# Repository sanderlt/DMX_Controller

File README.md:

# DMX512 LED Controller
Arduino DMX Controller. 48(16RGB) outputs. Based on 74HC595 Shift Registers.
Working voltage from 5 to 24v.

Files created in KiCad 7.0.1 and Arduino IDE 2.2.1

Firmware contain 20 programs. To switch betwin program please choose DMX address and fader to use specific program(see dmx_ctrl_nano_v.1.ino line 124 for options).

Planning to add smd AVR(or ARM) version

Demo video:

KiCad 3d wiew:

KiCad PCB editor view:

Assembly Process(you can see earliest pcb version):

Final View:

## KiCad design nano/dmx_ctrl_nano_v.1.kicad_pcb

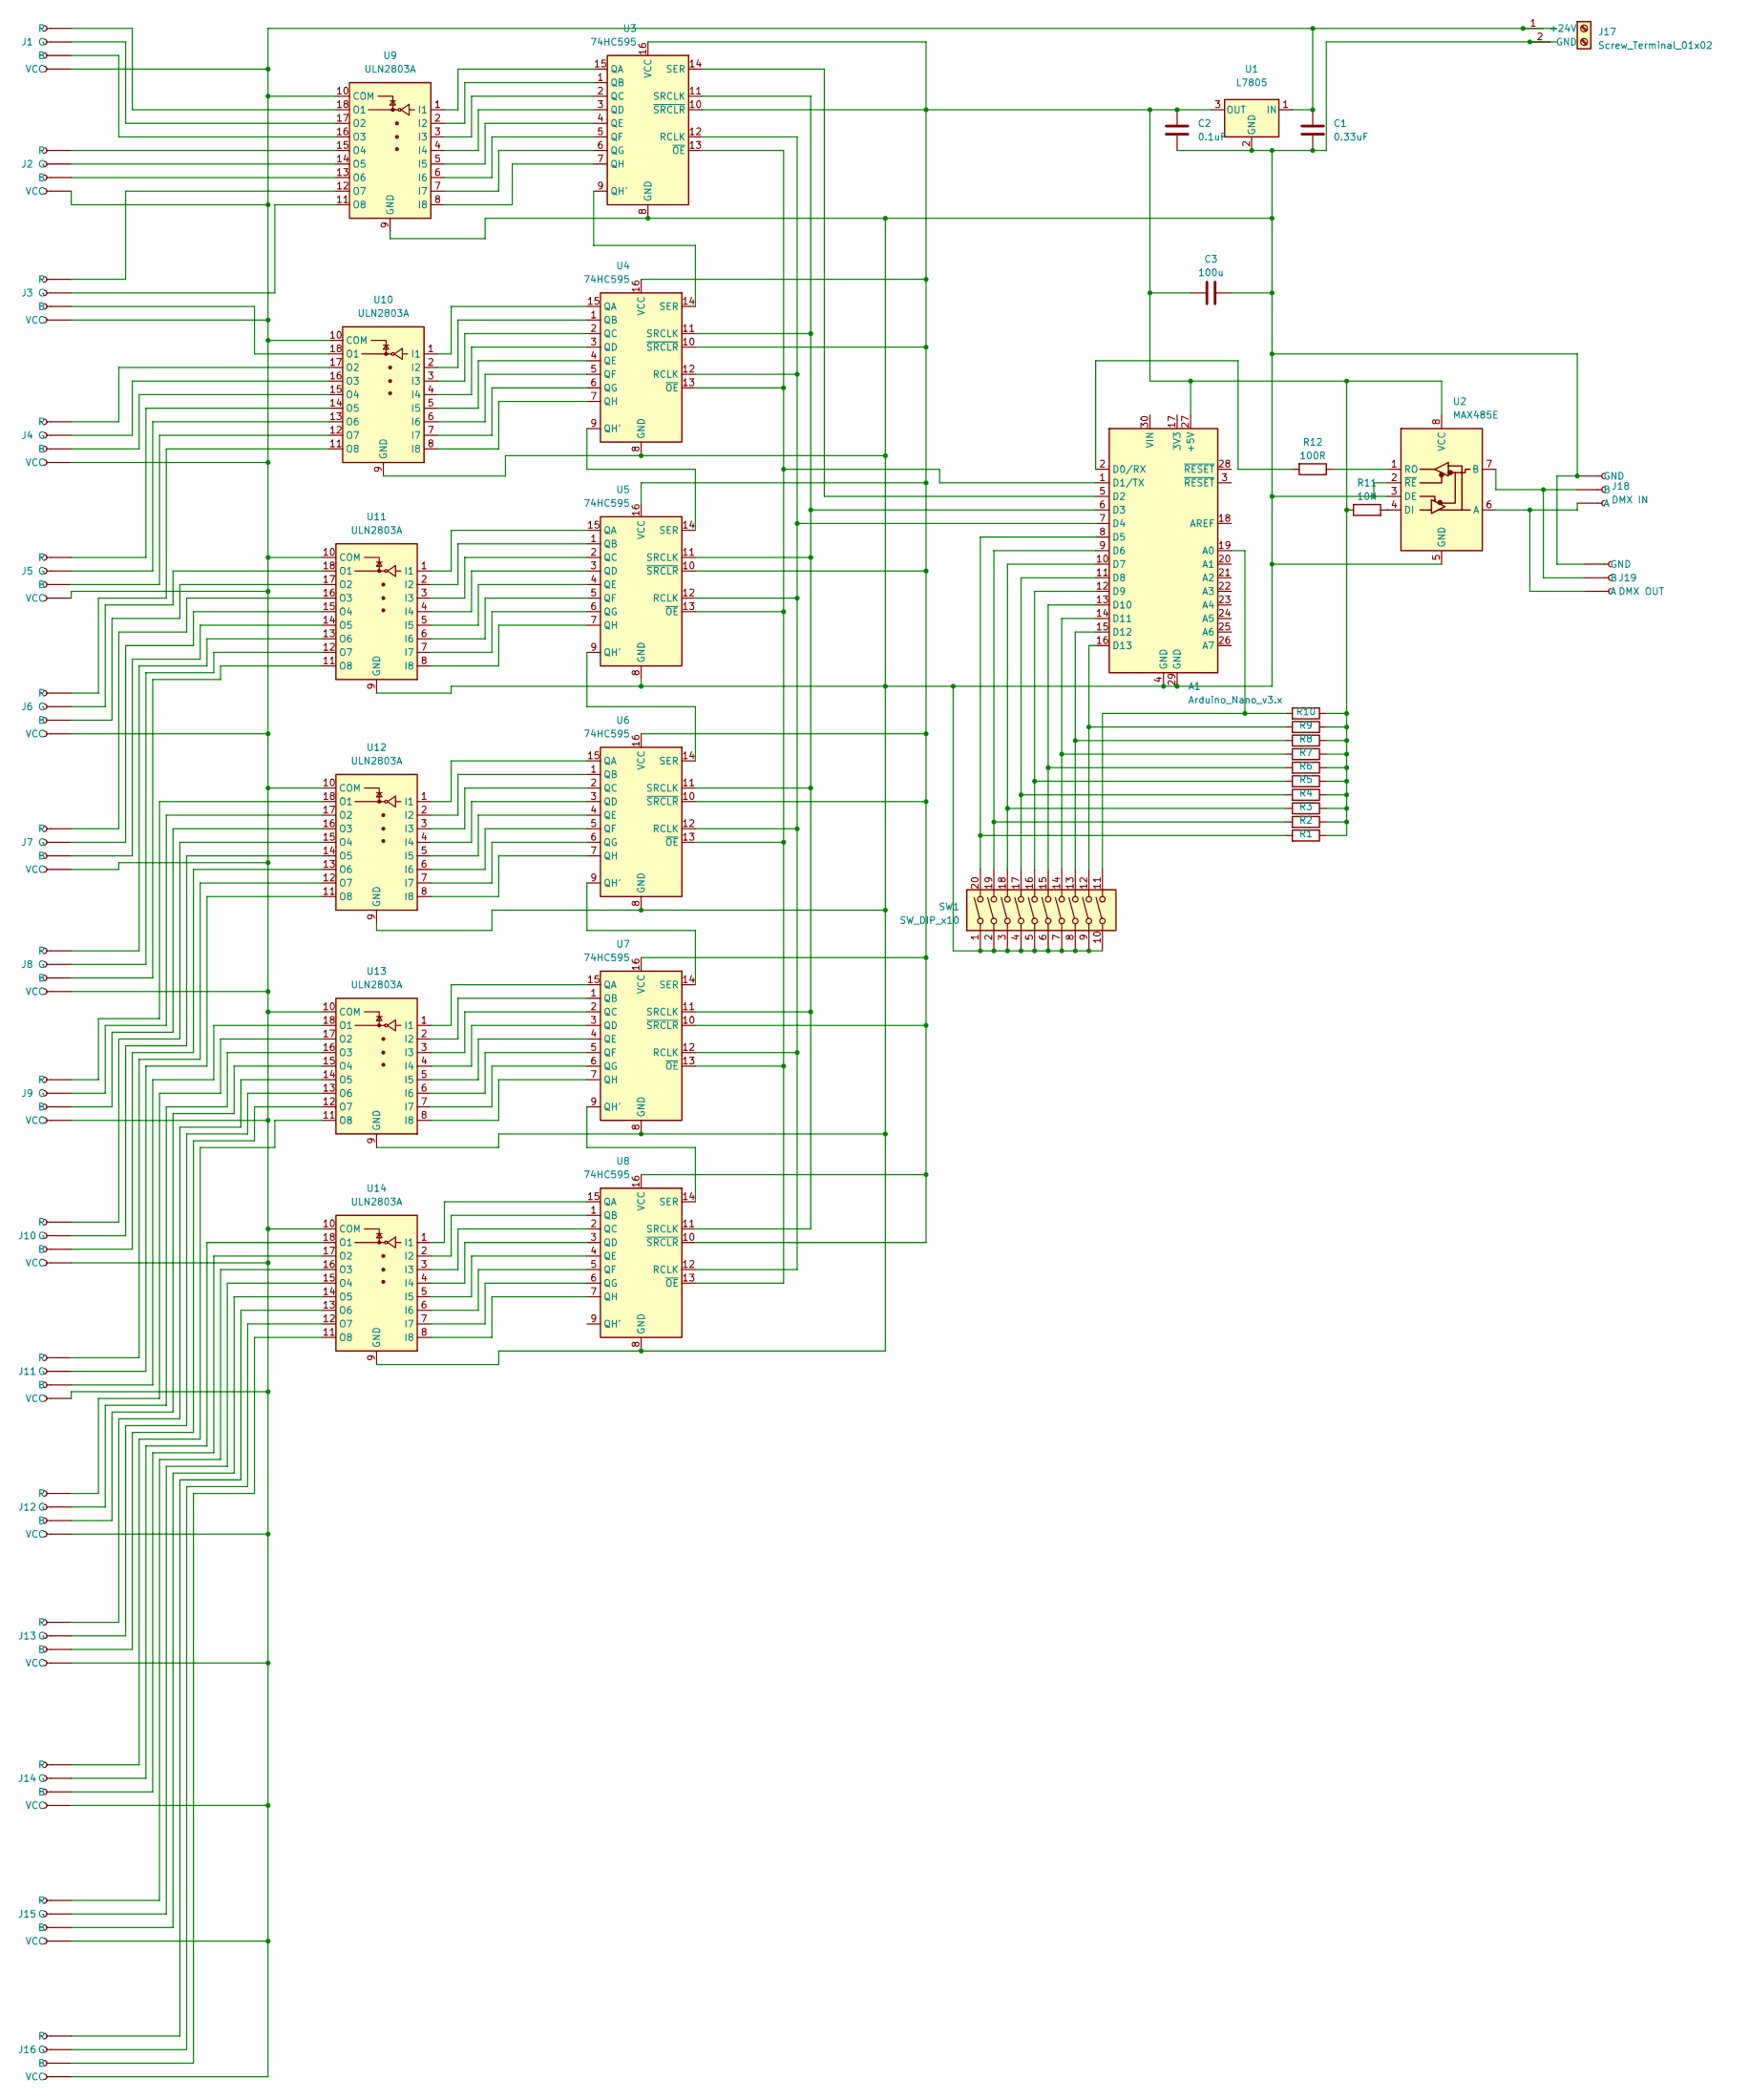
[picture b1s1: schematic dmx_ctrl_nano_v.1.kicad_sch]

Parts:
A1: Arduino_Nano_v3.x; Arduino_Nano
C1: 0.33uF; C_Axial_L3.8mm_D2.6mm_P7.50mm_Horizontal
C2: 0.1uF; C_Axial_L3.8mm_D2.6mm_P7.50mm_Horizontal
C3: 100u; C_Axial_L3.8mm_D2.6mm_P7.50mm_Horizontal
J1, J2, J3, J4, J5, J6, J7, J8, J9, J10, J11, J12, J13, J14, J15, J16: Conn_01x04_Female; TerminalBlock_4Ucon_1x04_P3.50mm_Vertical
J17: Screw_Terminal_01x02; TerminalBlock_bornier-2_P5.08mm
J18: DMX IN; TerminalBlock_4Ucon_1x03_P3.50mm_Vertical
J19: DMX OUT; TerminalBlock_4Ucon_1x03_P3.50mm_Vertical
R1, R2, R3, R4, R5, R6, R7, R8, R9, R10, R11: 10K; R_Axial_DIN0207_L6.3mm_D2.5mm_P2.54mm_Vertical
R12: 100R; R_Axial_DIN0207_L6.3mm_D2.5mm_P2.54mm_Vertical
SW1: SW_DIP_x10; DIP-20_W7.62mm
U1: L7805; TO-220F-3_Horizontal_TabDown
U2: MAX485E; DIP-8_W7.62mm
U3, U4, U5, U6, U7, U8: 74HC595; DIP-16_W7.62mm
U9, U10, U11, U12, U13, U14: ULN2803A; DIP-18_W7.62mm_LongPads

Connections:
unnamed: A1.27 (+5V), C2.1, C3.1, R1.1, R2.1, R3.1, R4.1, R5.1, R6.1, R7.1, R8.1, R9.1, R10.1, R11.1, U1.3 (OUT), U2.8 (VCC), U3.10 (~SRCLR), U3.16 (VCC), U4.10 (~SRCLR), U4.16 (VCC), U5.10 (~SRCLR), U5.16 (VCC), U6.10 (~SRCLR), U6.16 (VCC), U7.10 (~SRCLR), U7.16 (VCC), U8.10 (~SRCLR), U8.16 (VCC)
unnamed: A1.19 (A0), R10.2, SW1.11
unnamed: A1.2 (D0/RX), R12.2
unnamed: A1.1 (D1/TX), U3.13 (~OE), U4.13 (~OE), U5.13 (~OE), U6.13 (~OE), U7.13 (~OE), U8.13 (~OE)
unnamed: A1.5 (D2), U3.14 (SER)
unnamed: A1.6 (D3), U3.11 (SRCLK), U4.11 (SRCLK), U5.11 (SRCLK), U6.11 (SRCLK), U7.11 (SRCLK), U8.11 (SRCLK)
unnamed: A1.7 (D4), U3.12 (RCLK), U4.12 (RCLK), U5.12 (RCLK), U6.12 (RCLK), U7.12 (RCLK), U8.12 (RCLK)
unnamed: A1.8 (D5), R1.2, SW1.20
unnamed: A1.9 (D6), R2.2, SW1.19
unnamed: A1.10 (D7), R3.2, SW1.18
unnamed: A1.11 (D8), R4.2, SW1.17
unnamed: A1.12 (D9), R5.2, SW1.16
unnamed: A1.13 (D10), R6.2, SW1.15
unnamed: A1.14 (D11), R7.2, SW1.14
unnamed: A1.15 (D12), R8.2, SW1.13
unnamed: A1.16 (D13), R9.2, SW1.12
unnamed: J1.3 (B), U9.16 (O3)
unnamed: J1.2 (G), U9.17 (O2)
unnamed: J1.1 (R), U9.18 (O1)
unnamed: C1.1, J1.4 (VCC), J2.4 (VCC), J3.4 (VCC), J4.4 (VCC), J5.4 (VCC), J6.4 (VCC), J7.4 (VCC), J8.4 (VCC), J9.4 (VCC), J10.4 (VCC), J11.4 (VCC), J12.4 (VCC), J13.4 (VCC), J14.4 (VCC), J15.4 (VCC), J16.4 (VCC), J17.1 (+24V), U1.1 (IN), U9.10 (COM), U10.10 (COM), U11.10 (COM), U12.10 (COM), U13.10 (COM), U14.10 (COM)
unnamed: J2.3 (B), U9.13 (O6)
unnamed: J2.2 (G), U9.14 (O5)
unnamed: J2.1 (R), U9.15 (O4)
unnamed: J3.3 (B), U10.18 (O1)
unnamed: J3.2 (G), U9.11 (O8)
unnamed: J3.1 (R), U9.12 (O7)
unnamed: J4.3 (B), U10.15 (O4)
unnamed: J4.2 (G), U10.16 (O3)
unnamed: J4.1 (R), U10.17 (O2)
unnamed: J5.3 (B), U10.12 (O7)
unnamed: J5.2 (G), U10.13 (O6)
unnamed: J5.1 (R), U10.14 (O5)
unnamed: J6.3 (B), U11.17 (O2)
unnamed: J6.2 (G), U11.18 (O1)
unnamed: J6.1 (R), U10.11 (O8)
unnamed: J7.3 (B), U11.14 (O5)
unnamed: J7.2 (G), U11.15 (O4)
unnamed: J7.1 (R), U11.16 (O3)
unnamed: J8.3 (B), U11.11 (O8)
unnamed: J8.2 (G), U11.12 (O7)
unnamed: J8.1 (R), U11.13 (O6)
unnamed: J9.3 (B), U12.16 (O3)
unnamed: J9.2 (G), U12.17 (O2)
unnamed: J9.1 (R), U12.18 (O1)
unnamed: J10.3 (B), U12.13 (O6)
unnamed: J10.2 (G), U12.14 (O5)
unnamed: J10.1 (R), U12.15 (O4)
unnamed: J11.3 (B), U13.18 (O1)
unnamed: J11.2 (G), U12.11 (O8)
unnamed: J11.1 (R), U12.12 (O7)
unnamed: J12.3 (B), U13.15 (O4)
unnamed: J12.2 (G), U13.16 (O3)
unnamed: J12.1 (R), U13.17 (O2)
unnamed: J13.3 (B), U13.12 (O7)
unnamed: J13.2 (G), U13.13 (O6)
unnamed: J13.1 (R), U13.14 (O5)
unnamed: J14.3 (B), U14.17 (O2)
unnamed: J14.2 (G), U14.18 (O1)
unnamed: J14.1 (R), U13.11 (O8)
unnamed: J15.3 (B), U14.14 (O5)
unnamed: J15.2 (G), U14.15 (O4)
unnamed: J15.1 (R), U14.16 (O3)
unnamed: J16.3 (B), U14.11 (O8)
unnamed: J16.2 (G), U14.12 (O7)
unnamed: J16.1 (R), U14.13 (O6)
unnamed: A1.4 (GND), A1.29 (GND), C1.2, C2.2, C3.2, J17.2 (GND), J18.1 (GND), J19.1 (GND), SW1.1, SW1.2, SW1.3, SW1.4, SW1.5, SW1.6, SW1.7, SW1.8, SW1.9, SW1.10, U1.2 (GND), U2.2 (~RE), U2.3 (DE), U2.5 (GND), U3.8 (GND), U4.8 (GND), U5.8 (GND), U6.8 (GND), U7.8 (GND), U8.8 (GND), U9.9 (GND), U10.9 (GND), U11.9 (GND), U12.9 (GND), U13.9 (GND), U14.9 (GND)
unnamed: J18.3 (A), J19.3 (A), U2.6 (A)
unnamed: J18.2 (B), J19.2 (B), U2.7 (B)
unnamed: R11.2, U2.4 (DI)
unnamed: R12.1, U2.1 (RO)
unnamed: U3.15 (QA), U9.1 (I1)
unnamed: U3.1 (QB), U9.2 (I2)
unnamed: U3.2 (QC), U9.3 (I3)
unnamed: U3.3 (QD), U9.4 (I4)
unnamed: U3.4 (QE), U9.5 (I5)
unnamed: U3.5 (QF), U9.6 (I6)
unnamed: U3.6 (QG), U9.7 (I7)
unnamed: U3.9 (QH'), U4.14 (SER)
unnamed: U3.7 (QH), U9.8 (I8)
unnamed: U4.9 (QH'), U5.14 (SER)
unnamed: U5.9 (QH'), U6.14 (SER)
unnamed: U6.9 (QH'), U7.14 (SER)
unnamed: U7.9 (QH'), U8.14 (SER)
unnamed: U4.15 (QA), U10.1 (I1)
unnamed: U4.1 (QB), U10.2 (I2)
unnamed: U4.2 (QC), U10.3 (I3)
unnamed: U4.3 (QD), U10.4 (I4)
unnamed: U4.4 (QE), U10.5 (I5)
unnamed: U4.5 (QF), U10.6 (I6)
unnamed: U4.6 (QG), U10.7 (I7)
unnamed: U4.7 (QH), U10.8 (I8)
unnamed: U5.15 (QA), U11.1 (I1)
unnamed: U5.1 (QB), U11.2 (I2)
unnamed: U5.2 (QC), U11.3 (I3)
unnamed: U5.3 (QD), U11.4 (I4)
unnamed: U5.4 (QE), U11.5 (I5)
unnamed: U5.5 (QF), U11.6 (I6)
unnamed: U5.6 (QG), U11.7 (I7)
unnamed: U5.7 (QH), U11.8 (I8)
unnamed: U6.15 (QA), U12.1 (I1)
unnamed: U6.1 (QB), U12.2 (I2)
unnamed: U6.2 (QC), U12.3 (I3)
unnamed: U6.3 (QD), U12.4 (I4)
unnamed: U6.4 (QE), U12.5 (I5)
unnamed: U6.5 (QF), U12.6 (I6)
unnamed: U6.6 (QG), U12.7 (I7)
unnamed: U6.7 (QH), U12.8 (I8)
unnamed: U7.15 (QA), U13.1 (I1)
unnamed: U7.1 (QB), U13.2 (I2)
unnamed: U7.2 (QC), U13.3 (I3)
unnamed: U7.3 (QD), U13.4 (I4)
unnamed: U7.4 (QE), U13.5 (I5)
unnamed: U7.5 (QF), U13.6 (I6)
unnamed: U7.6 (QG), U13.7 (I7)
unnamed: U7.7 (QH), U13.8 (I8)
unnamed: U8.15 (QA), U14.1 (I1)
unnamed: U8.1 (QB), U14.2 (I2)
unnamed: U8.2 (QC), U14.3 (I3)
unnamed: U8.3 (QD), U14.4 (I4)
unnamed: U8.4 (QE), U14.5 (I5)
unnamed: U8.5 (QF), U14.6 (I6)
unnamed: U8.6 (QG), U14.7 (I7)
unnamed: U8.7 (QH), U14.8 (I8)

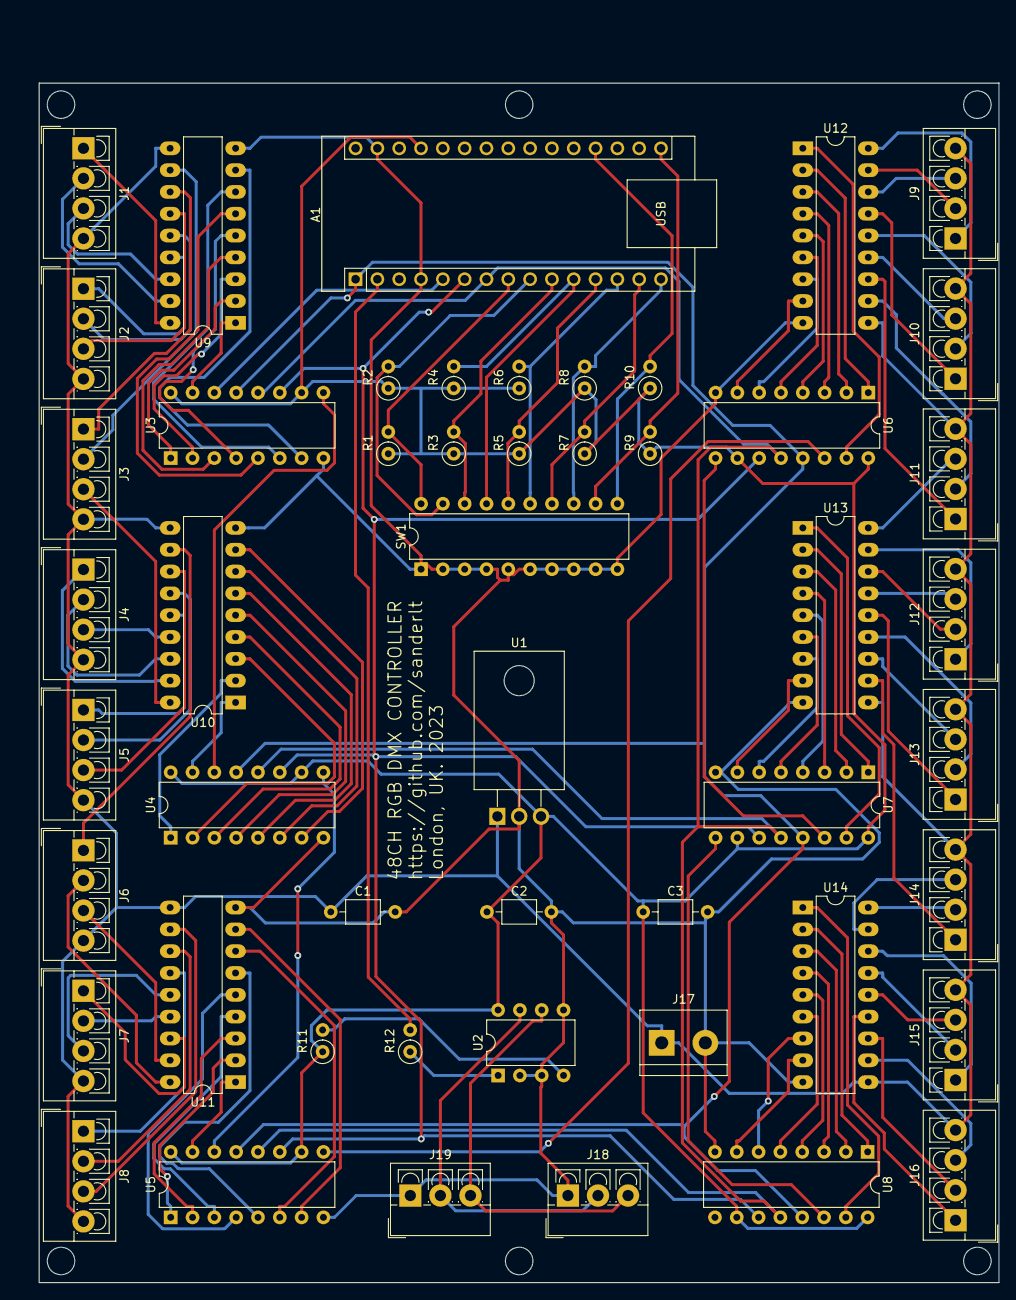
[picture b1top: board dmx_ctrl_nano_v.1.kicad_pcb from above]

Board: 2 copper layers, 114.3 x 147.3 mm, 50 parts (0 on the bottom side), 123 nets.

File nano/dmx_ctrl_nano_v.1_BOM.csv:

"Id";"Designator";"Footprint";"Quantity";"Designation";"Supplier and ref";
1;"J13,J15,J14,J11,J9,J1,J8,J10,J5,J3,J2,J4,J16,J7,J12,J6";"TerminalBlock_4Ucon_1x04_P3.50mm_Vertical";16;"Conn_01x04_Female";;;
2;"U1";"TO-220F-3_Horizontal_TabDown";1;"L7805";;;
3;"U8,U5,U4,U7,U3,U6";"DIP-16_W7.62mm";6;"74HC595";;;
4;"U2";"DIP-8_W7.62mm";1;"MAX485E";;;
5;"U11,U9,U14,U13,U10,U12";"DIP-18_W7.62mm_LongPads";6;"ULN2803A";;;
6;"R5,R9,R3,R2,R4,R6,R7,R8,R1,R10,R11";"R_Axial_DIN0207_L6.3mm_D2.5mm_P2.54mm_Vertical";11;"10K";;;
7;"J19";"TerminalBlock_4Ucon_1x03_P3.50mm_Vertical";1;"DMX OUT";;;
8;"C2";"C_Axial_L3.8mm_D2.6mm_P7.50mm_Horizontal";1;"0.1uF";;;
9;"R12";"R_Axial_DIN0207_L6.3mm_D2.5mm_P2.54mm_Vertical";1;"100R";;;
10;"SW1";"DIP-20_W7.62mm";1;"SW_DIP_x10";;;
11;"C3";"C_Axial_L3.8mm_D2.6mm_P7.50mm_Horizontal";1;"100u";;;
12;"J17";"TerminalBlock_bornier-2_P5.08mm";1;"VCC GND";;;
13;"J18";"TerminalBlock_4Ucon_1x03_P3.50mm_Vertical";1;"DMX IN";;;
14;"A1";"Arduino_Nano";1;"Arduino_Nano_v3.x";;;
15;"C1";"C_Axial_L3.8mm_D2.6mm_P7.50mm_Horizontal";1;"0.33uF";;;

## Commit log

2023-04-30 Rename 0001.csv to BOM.csv
2024-01-06 Create nano
2024-01-06 Create v1
2024-01-06 Rename dmx_ctrl_nano_v.1.kicad_pro to nano/dmx_ctrl_nano_v.1.kicad_pro
2024-01-06 Create media
